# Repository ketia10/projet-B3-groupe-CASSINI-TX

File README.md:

Bonjour,

Vous trouverez dans "Fichiers inventor" 2 sous-dossiers :
        - "Fichiers IPT et IAM" pour toutes les pièces créées.
        - "Fichiers STEP" pour l'assemblage de l'ensemble.

L'équipe Cassini T-X

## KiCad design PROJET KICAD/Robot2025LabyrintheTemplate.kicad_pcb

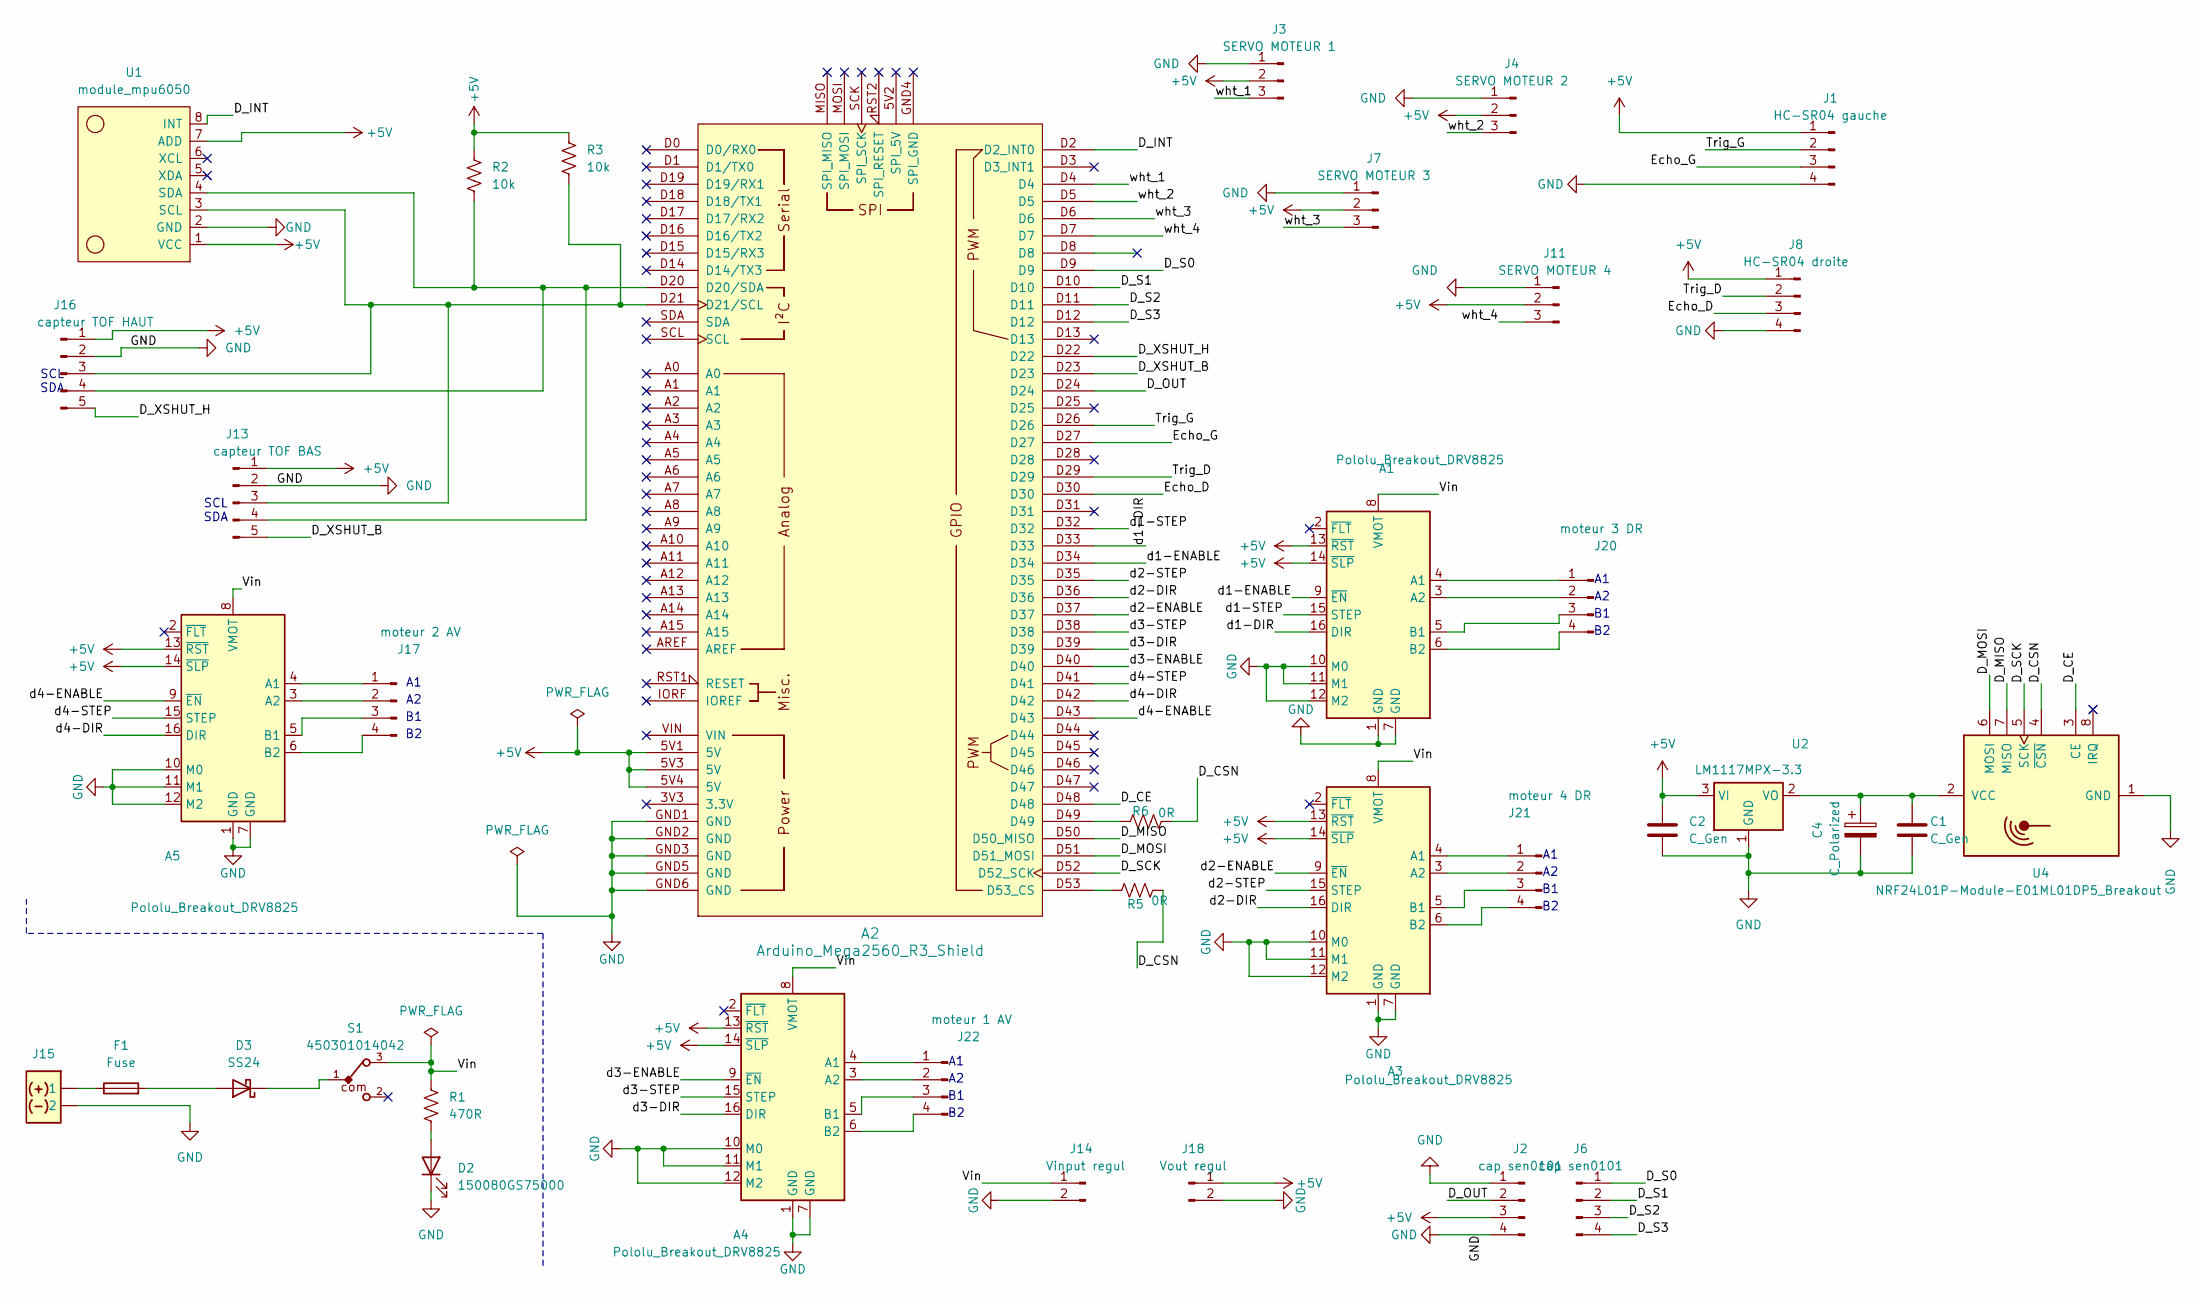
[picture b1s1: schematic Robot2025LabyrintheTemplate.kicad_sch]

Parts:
A1, A3, A4, A5: Pololu_Breakout_DRV8825; Pololu_Breakout-16_15.2x20.3mm
A2: Arduino_Mega2560_R3_Shield
C1, C2: C_Gen; C_1206_3216Metric_Pad1.33x1.80mm_HandSolder
C4: C_Polarized; CP_EIA-6032-28_Kemet-C_Pad2.25x2.35mm_HandSolder
D2: 150080GS75000; LED_0805_2012Metric_Pad1.15x1.40mm_HandSolder
D3: SS24; D_SMB_Handsoldering
F1: Fuse; Fuseholder_TR5_Littelfuse_No560_No460
J1: HC-SR04 gauche; JST_XH_B4B-XH-AM_1x04_P2.50mm_Long_Vertical
J2, J6: cap sen0101; JST_XH_B4B-XH-AM_1x04_P2.50mm_Long_Vertical
J3: SERVO MOTEUR 1; PinHeader_1x03_P2.54mm_Long_Vertical
J4: SERVO MOTEUR 2; PinHeader_1x03_P2.54mm_Long_Vertical
J7: SERVO MOTEUR 3; PinHeader_1x03_P2.54mm_Long_Vertical
J8: HC-SR04 droite; JST_XH_B4B-XH-AM_1x04_P2.50mm_Long_Vertical
J11: SERVO MOTEUR 4; PinHeader_1x03_P2.54mm_Long_Vertical
J13: capteur TOF BAS; JST_XH_B5B-XH-AM_1x05_P2.50mm_Long_Vertical
J14: Vinput regul; JST_XH_B2B-XH-AM_1x02_P2.50mm_Long_Vertical
J15: CON 1x2 POLARIZED; AMASS_XT60-F_1x02_P7.20mm_Vertical
J16: capteur TOF HAUT; JST_XH_B5B-XH-AM_1x05_P2.50mm_Long_Vertical
J17: moteur 2 AV; JST_XH_B4B-XH-AM_1x04_P2.50mm_Long_Vertical
J18: Vout regul; JST_XH_B2B-XH-AM_1x02_P2.50mm_Long_Vertical
J20: moteur 3 DR; JST_XH_B4B-XH-AM_1x04_P2.50mm_Long_Vertical
J21: moteur 4 DR; JST_XH_B4B-XH-AM_1x04_P2.50mm_Long_Vertical
J22: moteur 1 AV; JST_XH_B4B-XH-AM_1x04_P2.50mm_Long_Vertical
R1: 470R; R_1206_3216Metric_Pad1.30x1.75mm_HandSolder; PartNumber Voir farde de resistance
R2, R3: 10k; R_1206_3216Metric_Pad1.30x1.75mm_HandSolder; PartNumber Voir farde de resistance
R5, R6: 0R; R_1206_3216Metric_Pad1.30x1.75mm_HandSolder; PartNumber Voir farde de resistance
S1: 450301014042
U1: module_mpu6050
U2: LM1117MPX-3.3; SOT-223-3_TabPin2
U4: NRF24L01P-Module-E01ML01DP5_Breakout; E01-ML01DP5

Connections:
+5V: A1.13 (~RST), A1.14 (~SLP), A2.5V1 (5V), A2.5V3 (5V), A2.5V4 (5V), A3.13 (~RST), A3.14 (~SLP), A4.13 (~RST), A4.14 (~SLP), A5.13 (~RST), A5.14 (~SLP), C2.1, J1.1, J2.3, J3.2, J4.2, J7.2, J8.1, J11.2, J13.1, J16.1, J18.1, R2.1, R3.1, U1.1 (VCC), U1.7 (ADD), U2.3 (VI)
/D_CE: A2.D48, U4.3 (CE)
/D_CSN: R5.2, R6.2, U4.4 (~CSN)
/D_INT: A2.D2 (D2_INT0), U1.8 (INT)
/D_MISO: A2.D50 (D50_MISO), U4.7 (MISO)
/D_MOSI: A2.D51 (D51_MOSI), U4.6 (MOSI)
/D_OUT: A2.D24, J2.2
/D_S0: A2.D9, J6.1
/D_S1: A2.D10, J6.2
/D_S2: A2.D11, J6.3
/D_S3: A2.D12, J6.4
/D_SCK: A2.D52 (D52_SCK), U4.5 (SCK)
/D_XSHUT_B: A2.D23, J13.5
/D_XSHUT_H: A2.D22, J16.5
/Echo_D: A2.D30, J8.3
/Echo_G: A2.D27, J1.3
/Trig_D: A2.D29, J8.2
/Trig_G: A2.D26, J1.2
/Vin: A1.8 (VMOT), A3.8 (VMOT), A4.8 (VMOT), A5.8 (VMOT), J14.1, R1.1, S1.3
/d1-DIR: A1.16 (DIR), A2.D33
/d1-ENABLE: A1.9 (~EN), A2.D34
/d1-STEP: A1.15 (STEP), A2.D32
/d2-DIR: A2.D36, A3.16 (DIR)
/d2-ENABLE: A2.D37, A3.9 (~EN)
/d2-STEP: A2.D35, A3.15 (STEP)
/d3-DIR: A2.D39, A4.16 (DIR)
/d3-ENABLE: A2.D40, A4.9 (~EN)
/d3-STEP: A2.D38, A4.15 (STEP)
/d4-DIR: A2.D42, A5.16 (DIR)
/d4-ENABLE: A2.D43, A5.9 (~EN)
/d4-STEP: A2.D41, A5.15 (STEP)
/wht_1: A2.D4, J3.3
/wht_2: A2.D5, J4.3
/wht_3: A2.D6, J7.3
/wht_4: A2.D7, J11.3
GND: A1.1 (GND), A1.7 (GND), A1.10 (M0), A1.11 (M1), A1.12 (M2), A2.GND1 (GND), A2.GND2 (GND), A2.GND3 (GND), A2.GND5 (GND), A2.GND6 (GND), A3.1 (GND), A3.7 (GND), A3.10 (M0), A3.11 (M1), A3.12 (M2), A4.1 (GND), A4.7 (GND), A4.10 (M0), A4.11 (M1), A4.12 (M2), A5.1 (GND), A5.7 (GND), A5.10 (M0), A5.11 (M1), A5.12 (M2), C1.2, C2.2, C4.2, D2.1 (K), J1.4, J2.1, J2.4, J3.1, J4.1, J7.1, J8.4, J11.1, J13.2, J14.2, J15.2, J16.2, J18.2, U1.2 (GND), U2.1 (GND), U4.1 (GND)
unnamed: A1.4 (A1), J20.1
unnamed: A1.3 (A2), J20.2
unnamed: A1.5 (B1), J20.3
unnamed: A1.6 (B2), J20.4
unnamed: A2.D20 (D20/SDA), J13.4, J16.4, R2.2, U1.4 (SDA)
unnamed: A2.D21 (D21/SCL), J13.3, J16.3, R3.2, U1.3 (SCL)
unnamed: A2.D53 (D53_CS), R5.1
unnamed: A2.D49, R6.1
unnamed: A3.4 (A1), J21.1
unnamed: A3.3 (A2), J21.2
unnamed: A3.5 (B1), J21.3
unnamed: A3.6 (B2), J21.4
unnamed: A4.4 (A1), J22.1
unnamed: A4.3 (A2), J22.2
unnamed: A4.5 (B1), J22.3
unnamed: A4.6 (B2), J22.4
unnamed: A5.4 (A1), J17.1
unnamed: A5.3 (A2), J17.2
unnamed: A5.5 (B1), J17.3
unnamed: A5.6 (B2), J17.4
unnamed: D2.2 (A), R1.2
unnamed: D3.2 (A), F1.2
unnamed: D3.1 (K), S1.1
unnamed: F1.1, J15.1
unnamed: C1.1, C4.1, U2.2 (VO), U4.2 (VCC)

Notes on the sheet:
SCL SDA

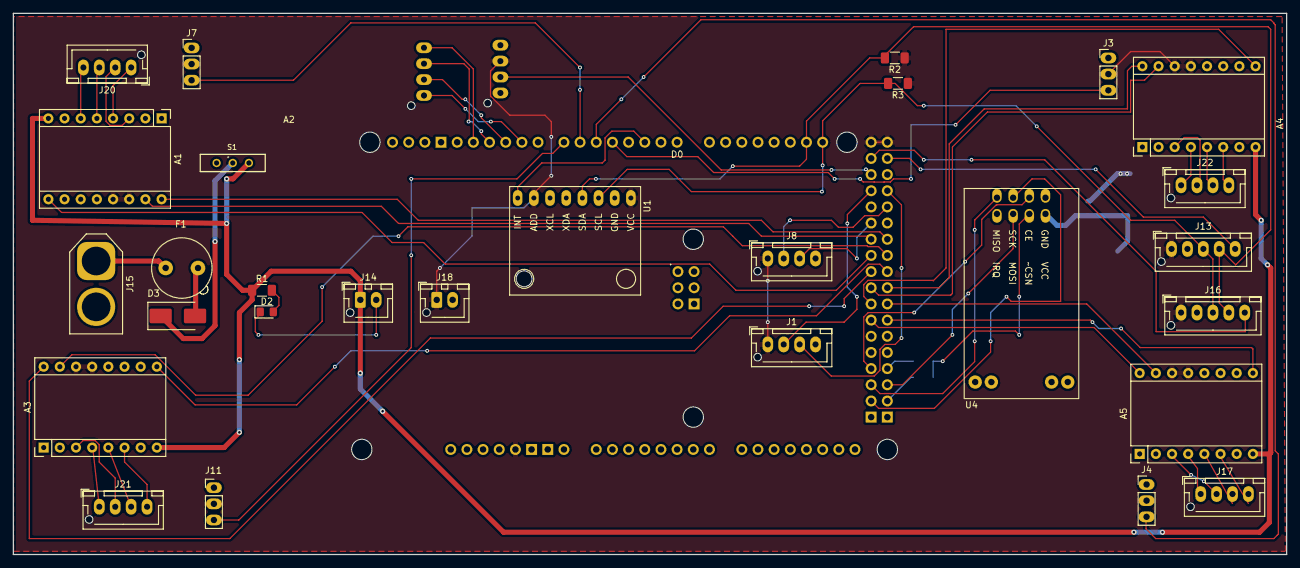
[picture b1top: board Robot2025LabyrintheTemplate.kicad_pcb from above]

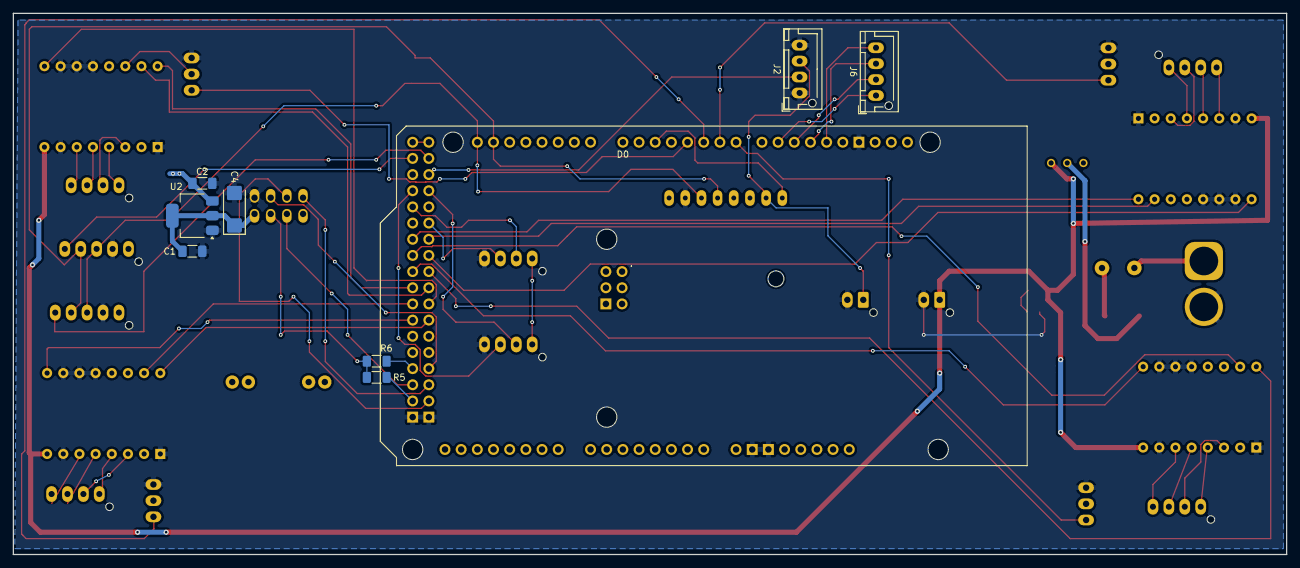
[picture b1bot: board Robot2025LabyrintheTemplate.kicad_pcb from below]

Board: 2 copper layers, 200.0 x 85.0 mm, 37 parts (8 on the bottom side), 61 nets.

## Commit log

2026-03-19 comit frist
2026-03-22 Create Inventor
2026-04-03 Create Fichiers Inventor
2026-04-17 sppression du code dans github inventor
2026-04-21 Create Kicad V1
2026-04-23 revue avec alaime
2026-04-23 test
2026-04-23 test2
2026-04-23 test3
2026-04-23 Remove .history folder
2026-04-23 test 4
2026-04-24 fin de la schematique, debut rotage
2026-04-24 rien
2026-04-24 routage 1
2026-04-24 pcbgo
2026-04-24 what
2026-04-24 gnd et 5v
2026-04-24 maj2
2026-04-24 next
2026-04-24 final
2026-04-26 finish
2026-04-29 Différentes modifs à discuter de vive voix
2026-05-13 Create Fichiers IPT et IAM
